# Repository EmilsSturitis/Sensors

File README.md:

# Sensors
Single repo for all of the sensor and interface breakout pcb's

Altimeter
HW:
Based on the TE MS581 sensor.
FW:
Based on the STM32F411

OPA548_dev  
Programmable CC/CV PSU

CAN Breakout

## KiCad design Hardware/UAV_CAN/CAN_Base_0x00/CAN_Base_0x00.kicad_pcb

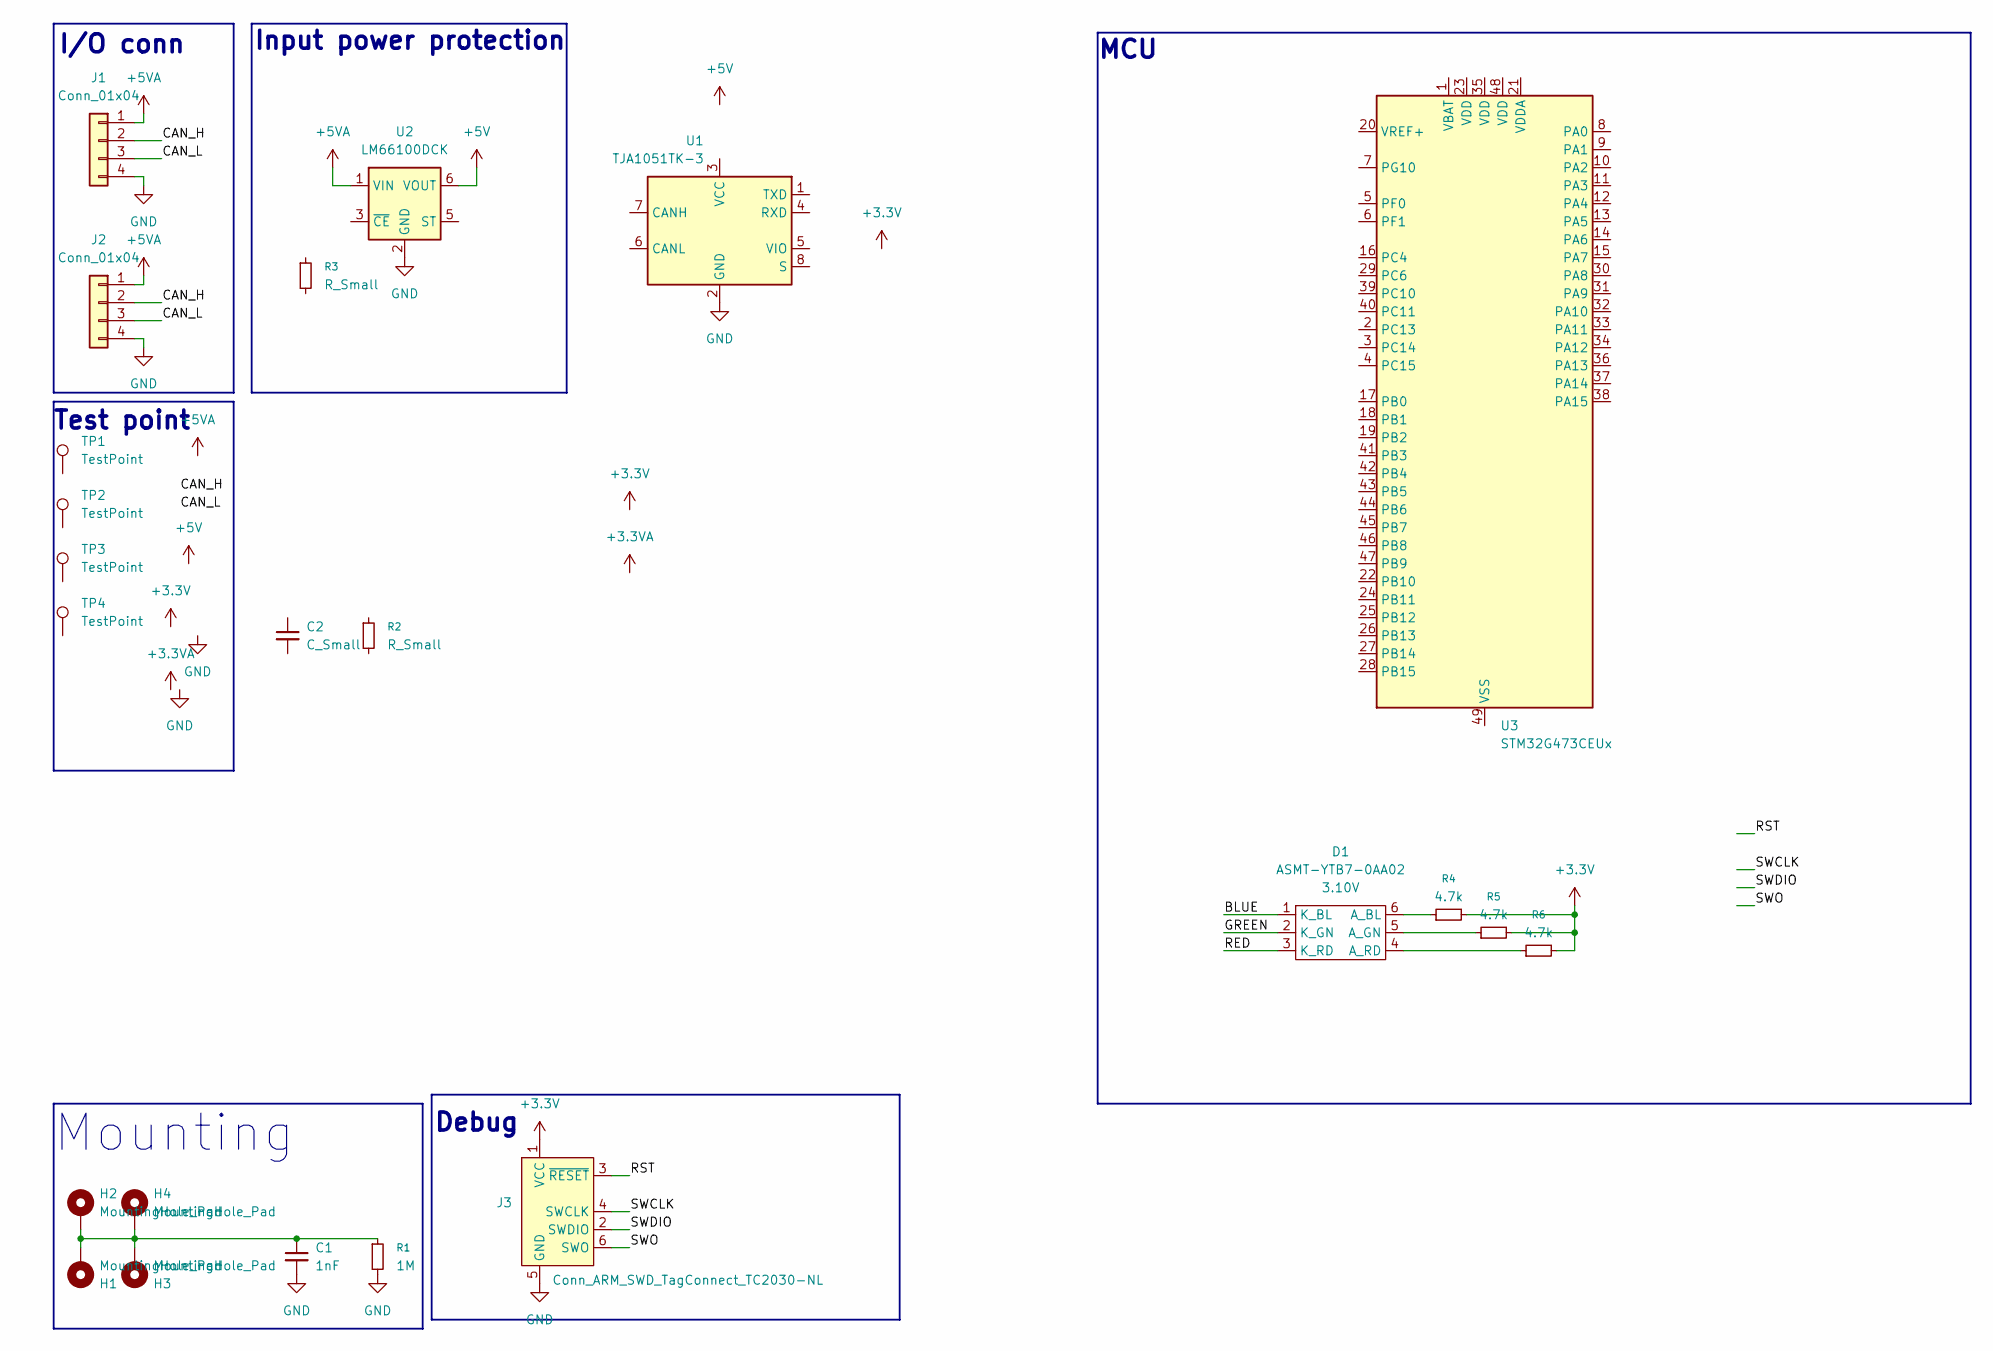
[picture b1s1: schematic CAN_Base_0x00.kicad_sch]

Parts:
C1: 1nF; C_0603_1608Metric
C2: C_Small; C_0603_1608Metric
D1: ASMT-YTB7-0AA02; ASMT-YTD7-0AA02
H1, H2, H3, H4: MountingHole_Pad; MountingHole_2.7mm_M2.5_Pad_Via
J1, J2: Conn_01x04; JST_GH_SM04B-GHS-TB_1x04-1MP_P1.25mm_Horizontal
J3: Conn_ARM_SWD_TagConnect_TC2030-NL; Tag-Connect_TC2030-IDC-NL_2x03_P1.27mm_Vertical
R1: 1M; R_0603_1608Metric
R2, R3: R_Small; R_0603_1608Metric
R4, R5, R6: 4.7k; R_0603_1608Metric
TP1, TP2, TP3, TP4: TestPoint; TestPoint_Pad_D1.0mm
U1: TJA1051TK-3; HVSON-8-1EP_3x3mm_P0.65mm_EP1.6x2.4mm
U2: LM66100DCK; SOT-363_SC-70-6
U3: STM32G473CEUx; QFN-48-1EP_7x7mm_P0.5mm_EP5.6x5.6mm

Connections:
+3.3V: J3.1 (VCC), R4.2, R5.2, R6.2
+5V: U2.6 (VOUT)
+5VA: J1.1, J2.1, U2.1 (VIN)
/BLUE: D1.1 (K_BL)
/CAN_H: J1.2, J2.2
/CAN_L: J1.3, J2.3
/GREEN: D1.2 (K_GN)
/RED: D1.3 (K_RD)
/RST: J3.3 (~RESET)
/SWCLK: J3.4 (SWCLK)
/SWDIO: J3.2 (SWDIO)
/SWO: J3.6 (SWO)
GND: C1.2, J1.4, J2.4, J3.5 (GND), R1.2, U1.2 (GND), U1.9 (GND), U2.2 (GND)
unnamed: C1.1, H1.1, H2.1, H3.1, H4.1, R1.1
unnamed: D1.6 (A_BL), R4.1
unnamed: D1.5 (A_GN), R5.1
unnamed: D1.4 (A_RD), R6.1

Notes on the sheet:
MCU
I/O conn
Test point
Input power protection
Debug
Mounting

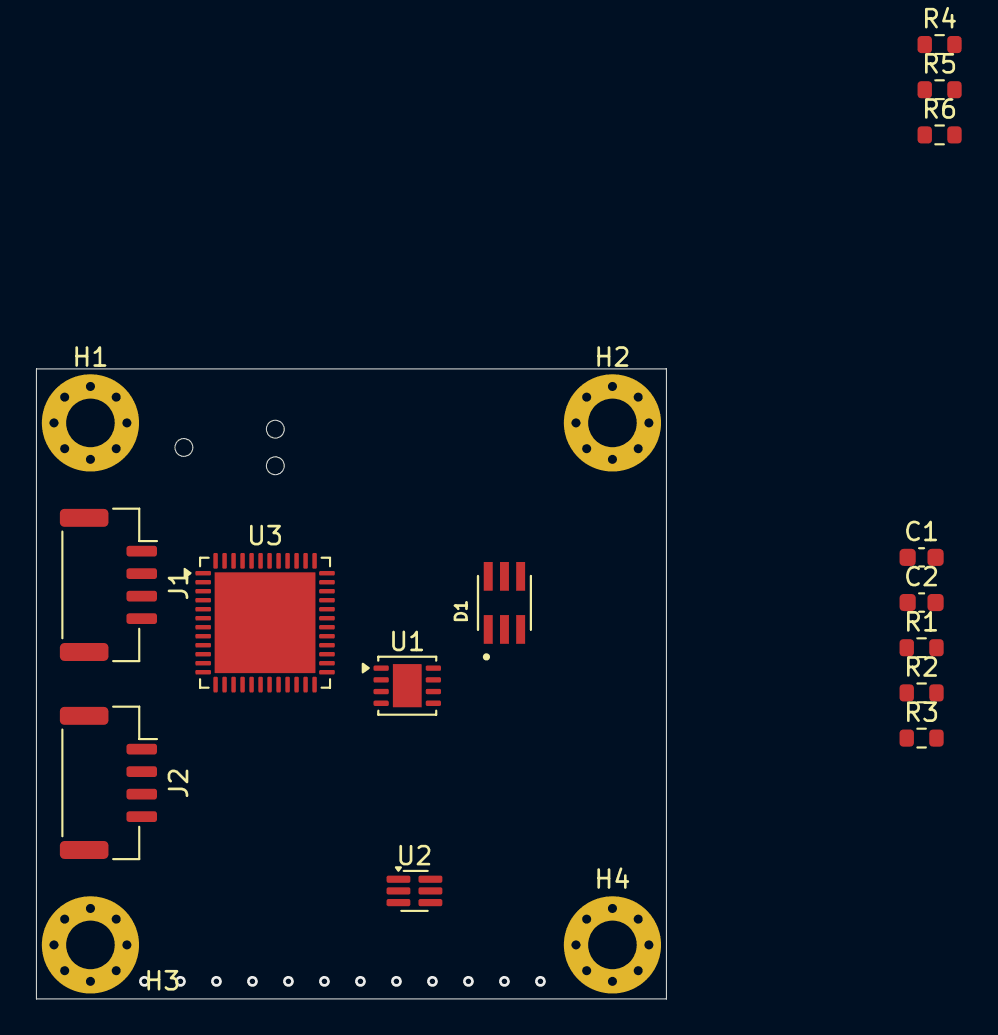
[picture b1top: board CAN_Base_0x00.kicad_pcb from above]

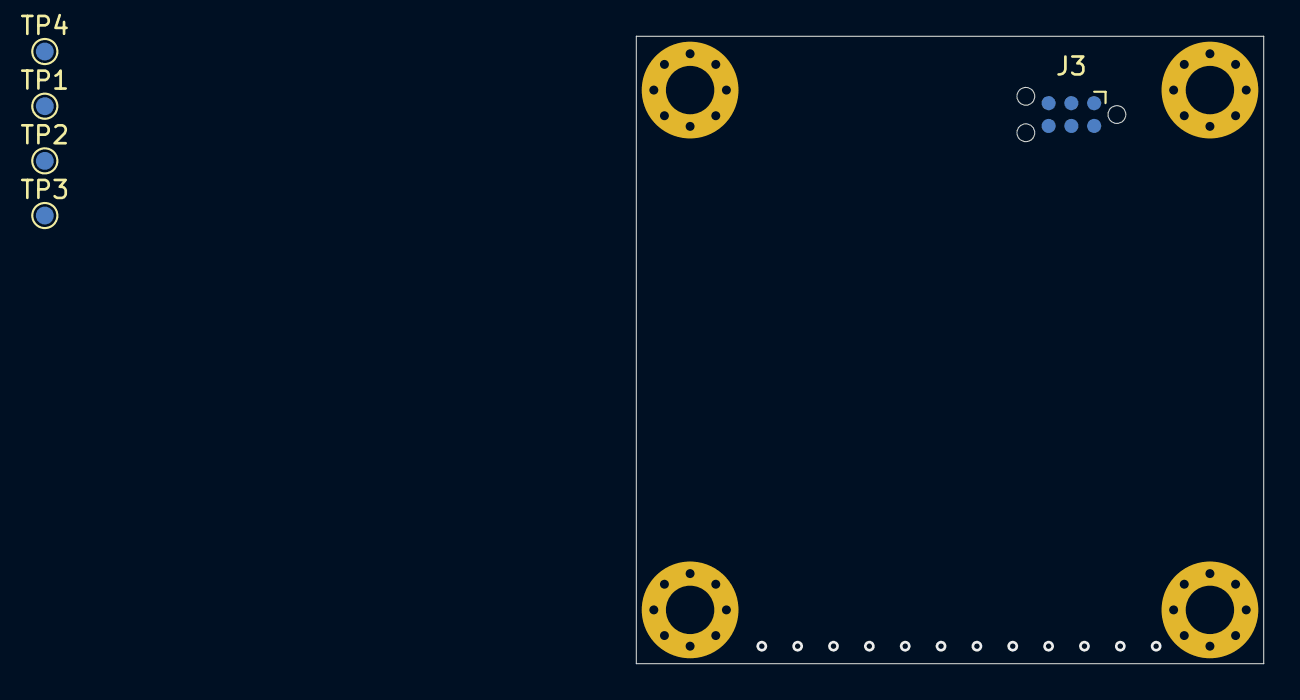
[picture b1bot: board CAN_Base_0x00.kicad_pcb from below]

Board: 2 copper layers, 35.0 x 35.0 mm, 23 parts (5 on the bottom side), 9 nets.

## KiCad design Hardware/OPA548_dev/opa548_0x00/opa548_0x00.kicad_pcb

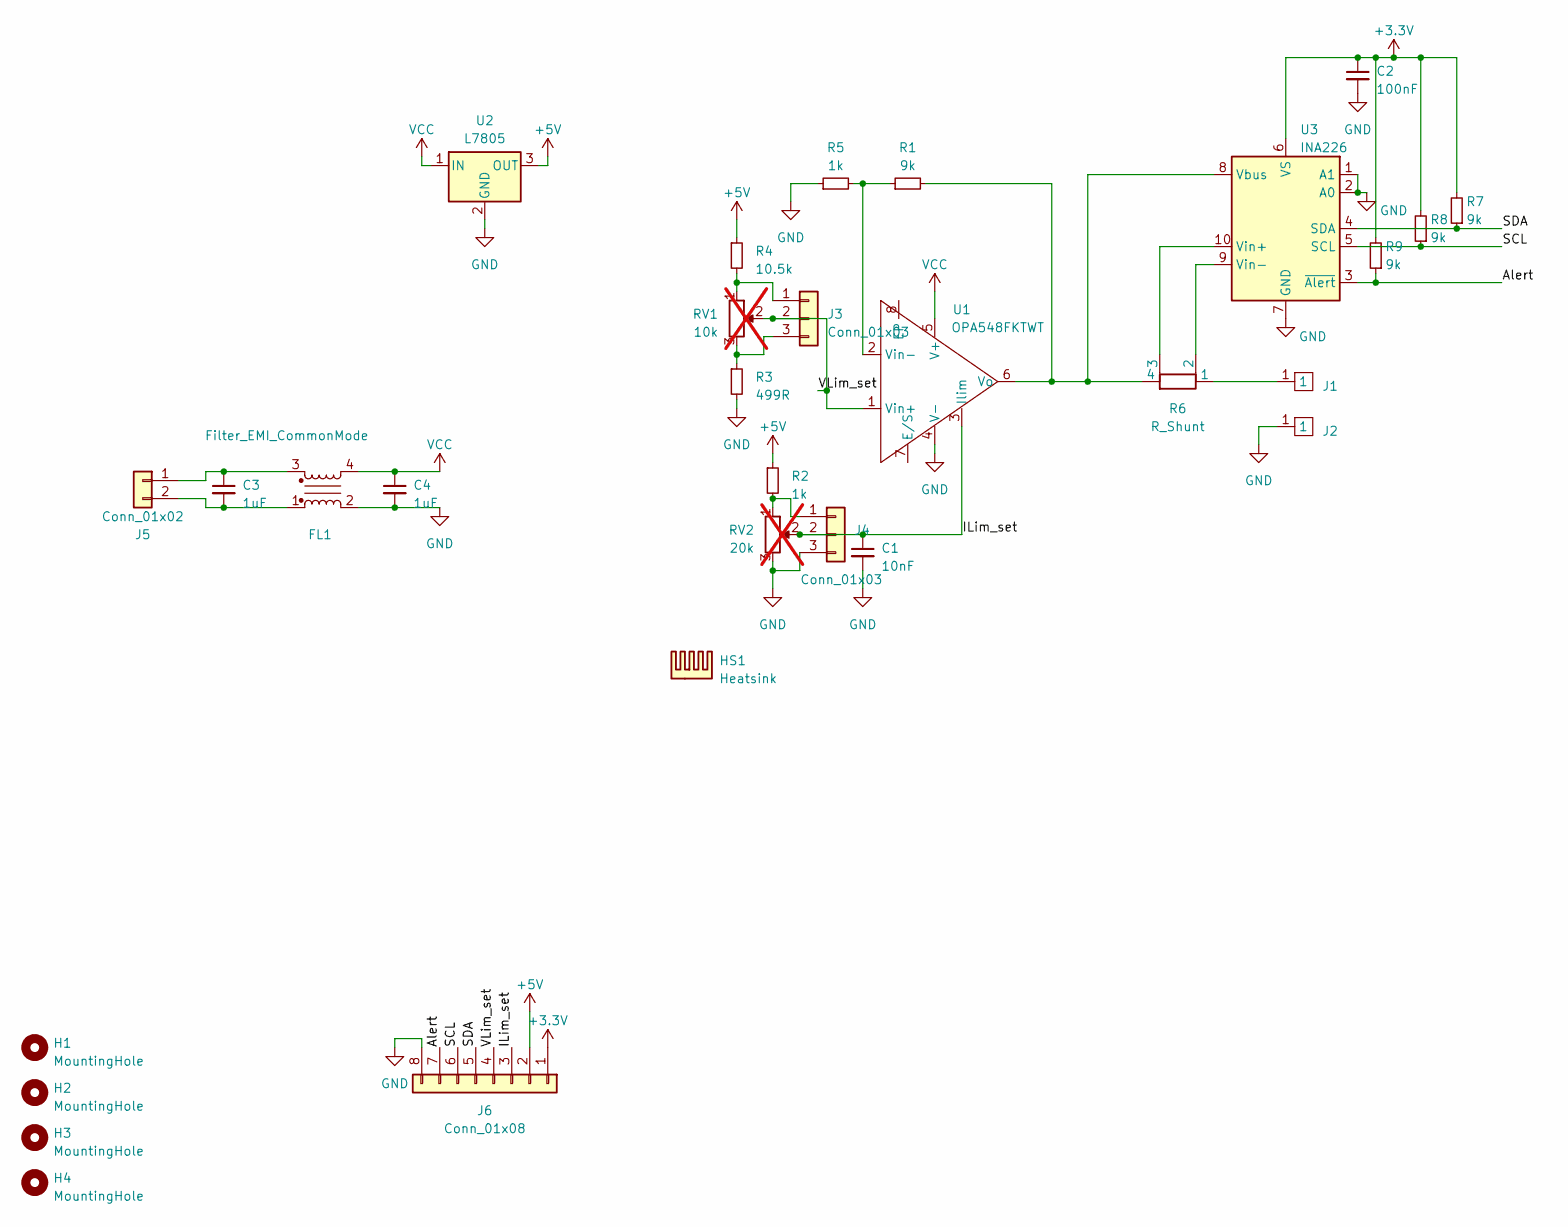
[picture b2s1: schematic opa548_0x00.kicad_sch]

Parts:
C1: 10nF; C_0805_2012Metric
C2: 100nF; C_0805_2012Metric
C3, C4: 1uF; C_1210_3225Metric
FL1: Filter_EMI_CommonMode; P0420NL
H1, H2, H3, H4: MountingHole; MountingHole_3.7mm
HS1: Heatsink; Heatsink_38x38mm_SpringFixation
J1, J2: CalTest_CT3151
J3, J4: Conn_01x03; JST_XH_B3B-XH-A_1x03_P2.50mm_Vertical
J5: Conn_01x02; TerminalBlock_bornier-2_P5.08mm
J6: Conn_01x08; PinHeader_1x08_P2.00mm_Vertical
R1, R7, R8, R9: 9k; R_0805_2012Metric
R2, R5: 1k; R_0805_2012Metric
R3: 499R; R_0805_2012Metric
R4: 10.5k; R_0805_2012Metric
R6: R_Shunt; R_Shunt_Vishay_WSKW0612
RV1: 10k; Potentiometer_Alpha_RD901F-40-00D_Single_Vertical_CircularH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; not fitted
RV2: 20k; Potentiometer_Alpha_RD901F-40-00D_Single_Vertical_CircularH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; not fitted
U1: OPA548FKTWT; TO-263-7_TabPin8
U2: L7805; TO-220F-3_Vertical
U3: INA226; VSSOP-10_3x3mm_P0.5mm

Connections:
+3.3V: C2.1, J6.1, R7.2, R8.2, R9.2, U3.6 (VS)
+5V: J6.2, R2.1, R4.1, U2.3 (OUT)
/Alert: J6.7, R9.1, U3.3 (~Alert)
/ILim_set: C1.1, J4.2, J6.3, RV2.2, U1.3 (Ilim)
/SCL: J6.6, R8.1, U3.5 (SCL)
/SDA: J6.5, R7.1, U3.4 (SDA)
/VLim_set: J3.2, J6.4, RV1.2, U1.1 (Vin+)
GND: C1.2, C2.2, C4.2, FL1.2, J2.1, J4.3, J6.8, R3.2, R5.1, RV2.3, U1.4 (V-), U2.2 (GND), U3.1 (A1), U3.2 (A0), U3.7 (GND)
unnamed: J1.1, R6.1
unnamed: J3.1, R4.2, RV1.1
unnamed: J3.3, R3.1, RV1.3
unnamed: J4.1, R2.2, RV2.1
unnamed: C3.1, FL1.3, J5.1
unnamed: C3.2, FL1.1, J5.2
unnamed: R1.1, R5.2, U1.2 (Vin-)
unnamed: R1.2, R6.4, U1.6 (Vo), U3.8 (Vbus)
unnamed: R6.3, U3.10 (Vin+)
unnamed: R6.2, U3.9 (Vin-)
VCC: C4.1, FL1.4, U1.5 (V+), U2.1 (IN)

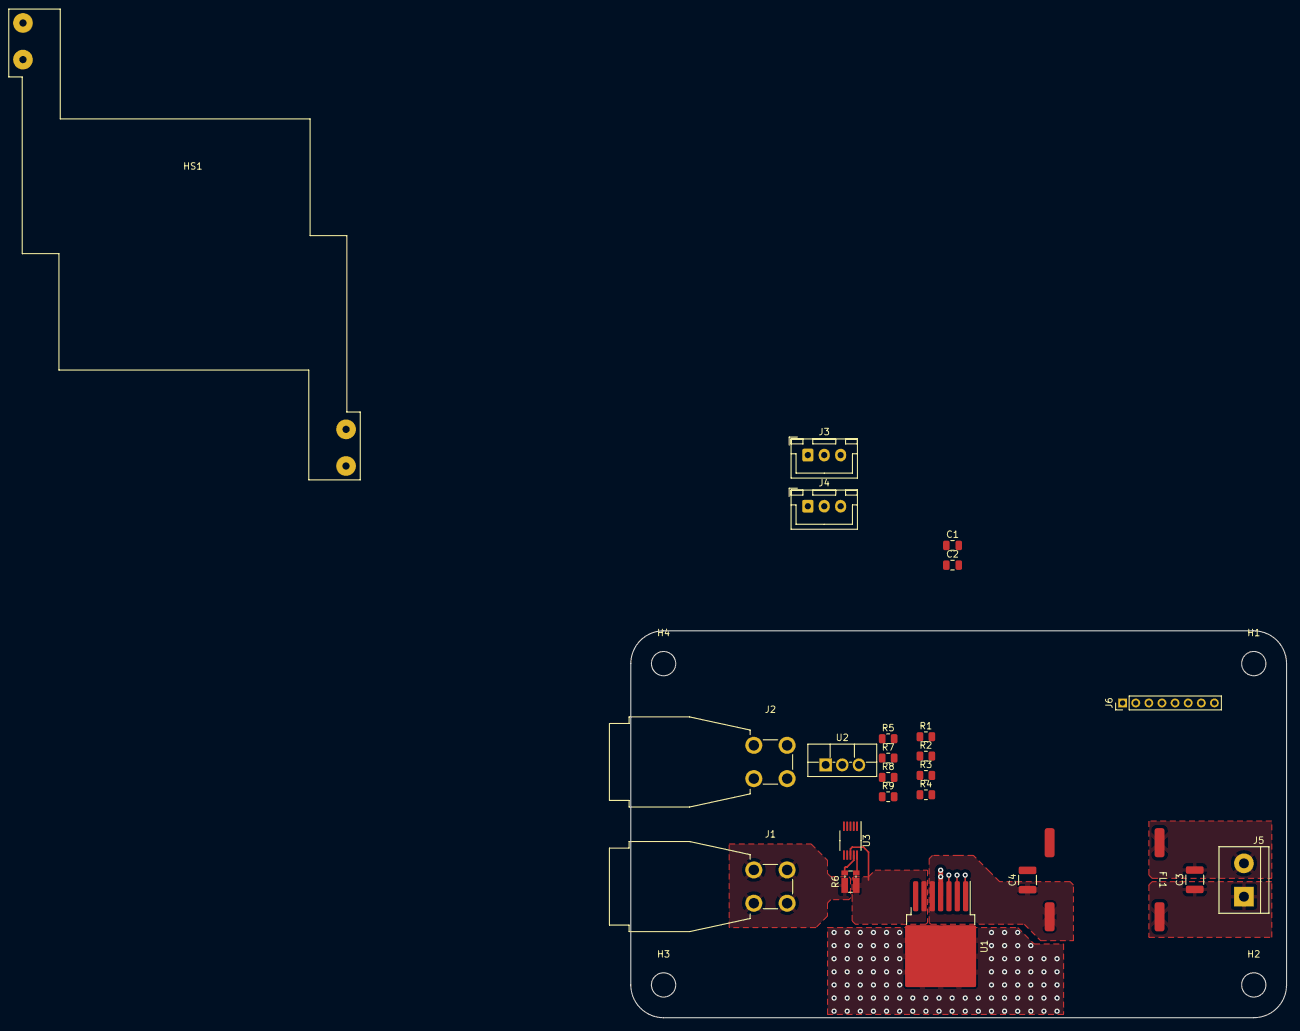
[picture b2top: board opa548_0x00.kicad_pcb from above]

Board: 2 copper layers, 100.0 x 59.0 mm, 28 parts (0 on the bottom side), 19 nets.

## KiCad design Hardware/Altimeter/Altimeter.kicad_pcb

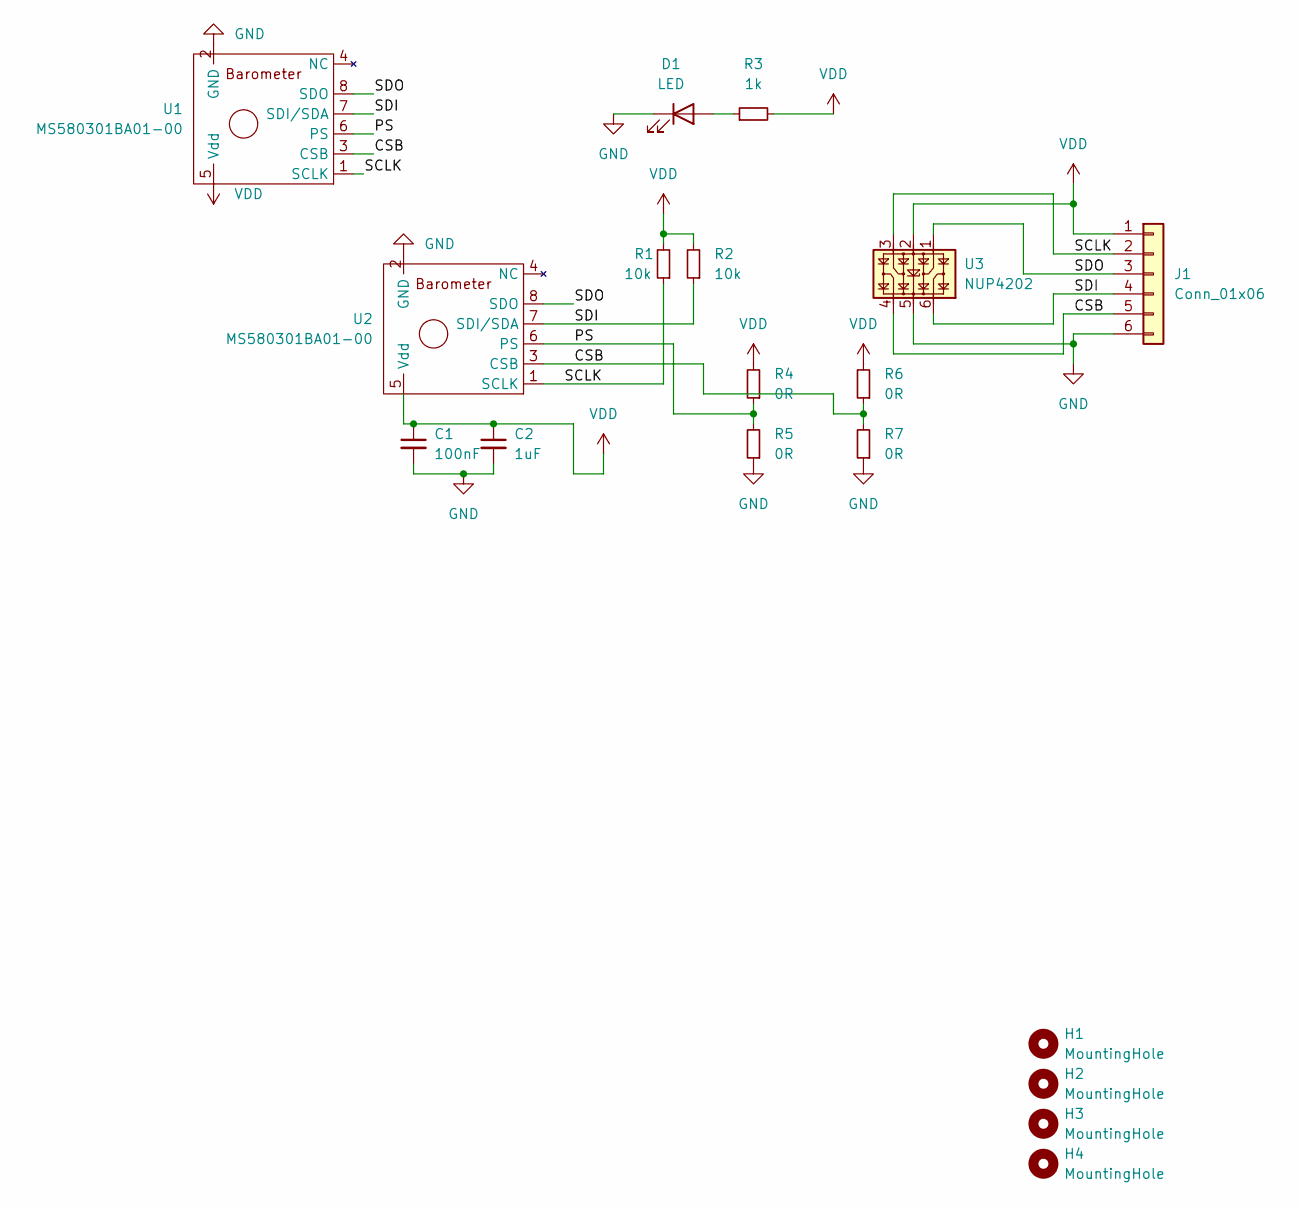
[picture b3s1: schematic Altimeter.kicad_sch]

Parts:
C1: 100nF; C_0805_2012Metric
C2: 1uF; C_0805_2012Metric
D1: LED; LED_PLCC-2
H1, H2, H3, H4: MountingHole; MountingHole_3.2mm_M3
J1: Conn_01x06; PinHeader_1x06_P2.54mm_Horizontal
R1, R2: 10k; R_0805_2012Metric
R3: 1k; R_0805_2012Metric
R4, R5, R6, R7: 0R; R_0805_2012Metric
U1, U2: MS580301BA01-00
U3: NUP4202; SOT-363_SC-70-6

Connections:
/CSB: J1.5, R6.1, R7.2, U1.3 (CSB), U2.3 (CSB), U3.4
/PS: R4.1, R5.2, U1.6 (PS), U2.6 (PS)
/SCLK: J1.2, R1.1, U1.1 (SCLK), U2.1 (SCLK), U3.3
/SDI: J1.4, R2.1, U1.7 (SDI/SDA), U2.7 (SDI/SDA), U3.6
/SDO: J1.3, U1.8 (SDO), U2.8 (SDO), U3.1
GND: C1.2, C2.2, D1.1 (K), J1.6, R5.1, R7.1, U1.2 (GND), U2.2 (GND), U3.5
unnamed: D1.2 (A), R3.1
VDD: C1.1, C2.1, J1.1, R1.2, R2.2, R3.2, R4.2, R6.2, U1.5 (Vdd), U2.5 (Vdd), U3.2

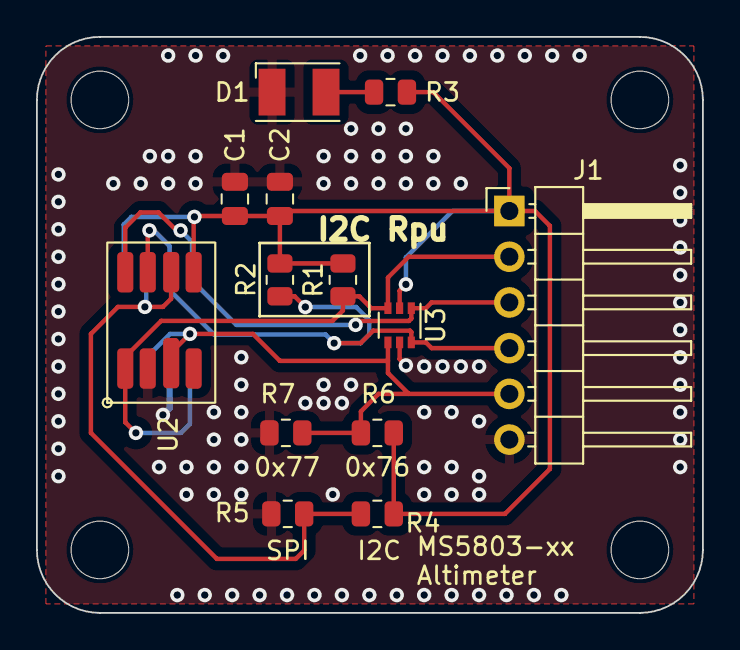
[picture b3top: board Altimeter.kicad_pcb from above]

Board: 2 copper layers, 37.0 x 32.0 mm, 18 parts (1 on the bottom side), 8 nets.

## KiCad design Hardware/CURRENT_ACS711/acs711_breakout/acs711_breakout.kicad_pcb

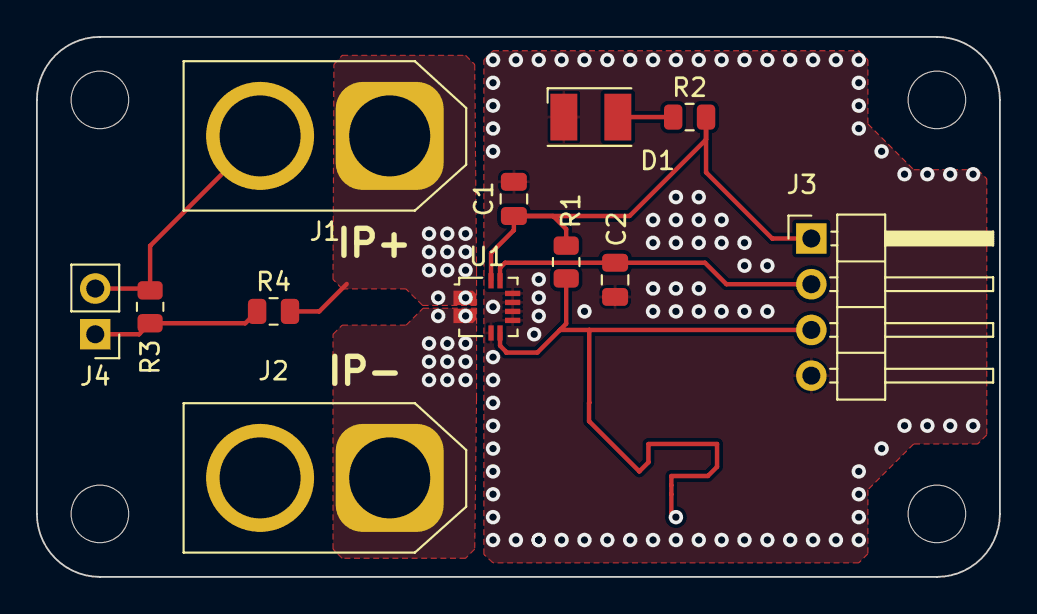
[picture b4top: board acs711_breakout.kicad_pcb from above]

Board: 2 copper layers, 53.5 x 30.0 mm, 16 parts (0 on the bottom side), 9 nets.

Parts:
C1: 100nF; C_0805_2012Metric
C2: DNP; C_0805_2012Metric
D1: LED; LED_PLCC-2
H1, H2, H3, H4: MountingHole; MountingHole_3.2mm_M3
J1: Conn_01x02; AMASS_XT60-M_1x02_P7.20mm_Vertical
J2: Conn_01x02; AMASS_XT60-F_1x02_P7.20mm_Vertical
J3: Conn_01x04; PinHeader_1x04_P2.54mm_Horizontal
J4: Conn_01x02; PinHeader_1x02_P2.54mm_Vertical
R1, R2: 1k; R_0805_2012Metric
R3, R4: R_Small; R_0805_2012Metric
U1: ACS711xEXLT-15AB; Allegro_QFN-12-10-1EP_3x3mm_P0.5mm

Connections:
GND: C1.2, C2.2, D1.1 (K), J3.4, U1.3 (GND), U1.5 (NC), U1.6 (NC), U1.7 (NC), U1.8 (NC)
unnamed: C2.1, J3.2, U1.9 (VIOUT)
unnamed: D1.2 (A), R2.1
unnamed: J1.2, J2.2, J4.2, R3.1
unnamed: J3.3, R1.2, U1.4 (~FAULT)
unnamed: J4.1, R3.2, R4.1
unnamed: J1.1, R4.2, U1.1 (IP+)
unnamed: J2.1, U1.2 (IP-)
VCC: C1.1, J3.1, R1.1, R2.2, U1.10 (VCC)

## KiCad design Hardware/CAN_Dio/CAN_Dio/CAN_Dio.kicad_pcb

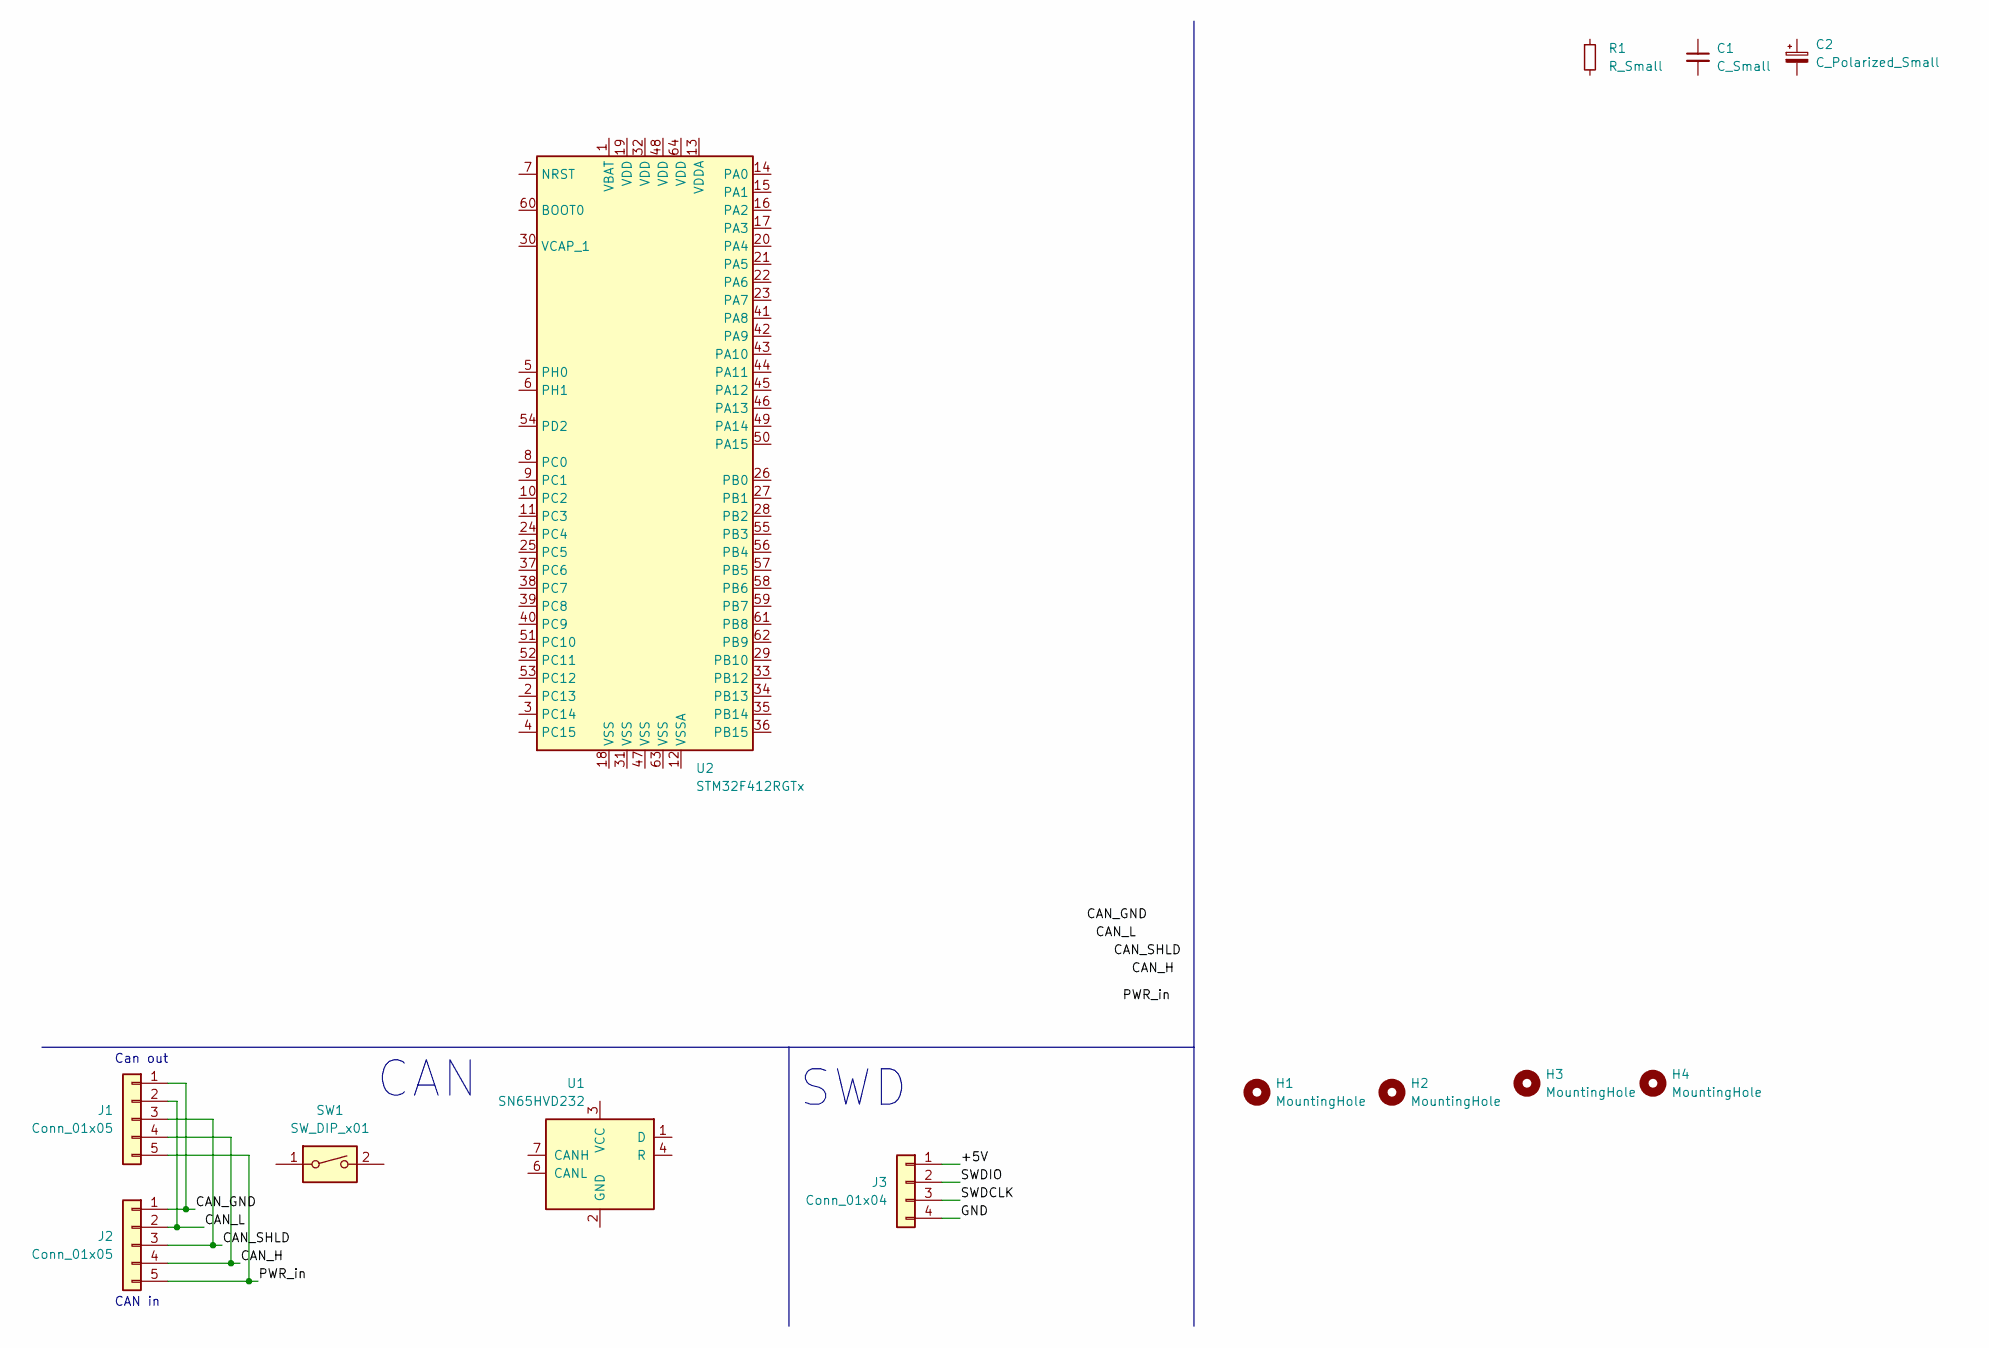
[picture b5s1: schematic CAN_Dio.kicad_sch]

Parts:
C1: C_Small; C_0805_2012Metric
C2: C_Polarized_Small
H1, H2, H3, H4: MountingHole; MountingHole_3.5mm
J1, J2: Conn_01x05; JST_XH_B5B-XH-A_1x05_P2.50mm_Vertical
J3: Conn_01x04; PinSocket_1x04_P2.54mm_Vertical
R1: R_Small; R_0805_2012Metric
SW1: SW_DIP_x01; SW_DIP_SPSTx01_Piano_10.8x4.1mm_W7.62mm_P2.54mm
U1: SN65HVD232; SOIC-8_3.9x4.9mm_P1.27mm
U2: STM32F412RGTx; LQFP-64_10x10mm_P0.5mm

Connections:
/+5V: J3.1
/CAN_GND: J1.1, J2.1
/CAN_H: J1.4, J2.4
/CAN_L: J1.2, J2.2
/CAN_SHLD: J1.3, J2.3
/GND: J3.4
/PWR_in: J1.5, J2.5
/SWDCLK: J3.3
/SWDIO: J3.2

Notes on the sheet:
CAN in
CAN
SWD
Can out

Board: 2 copper layers, 12 parts (0 on the bottom side), 5 nets, no tracks yet.

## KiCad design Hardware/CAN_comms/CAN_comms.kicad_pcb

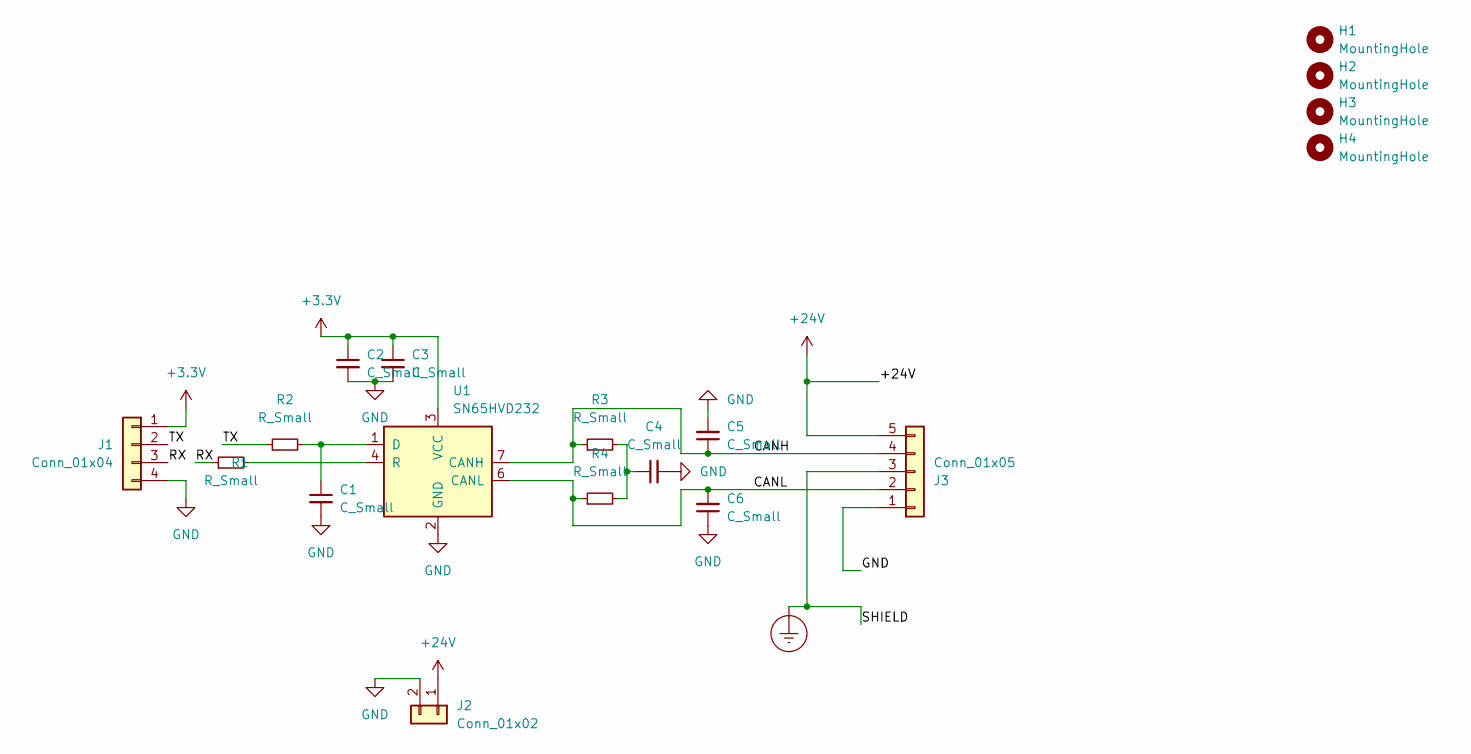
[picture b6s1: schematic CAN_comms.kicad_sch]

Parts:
C1, C2, C3, C4, C5, C6: C_Small; C_0805_2012Metric
H1, H2, H3, H4: MountingHole; MountingHole_3.2mm_M3_Pad_Via
J1: Conn_01x04; JST_XH_S4B-XH-A_1x04_P2.50mm_Horizontal
J2: Conn_01x02; JST_XH_S2B-XH-A_1x02_P2.50mm_Horizontal
J3: Conn_01x05; JST_XH_S5B-XH-A_1x05_P2.50mm_Horizontal
R1, R2: R_Small; R_0805_2012Metric
R3, R4: R_Small; R_1210_3225Metric
U1: SN65HVD232; SOIC-8_3.9x4.9mm_P1.27mm

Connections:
+3.3V: C2.1, C3.1, J1.1, U1.3 (VCC)
+24V: J2.1, J3.5
/CANH: C5.1, J3.4, R3.1, U1.7 (CANH)
/CANL: C6.2, J3.2, R4.1, U1.6 (CANL)
/RX: J1.3, R1.1
/TX: J1.2, R2.1
Earth_Protective: J3.3
GND: C1.2, C2.2, C3.2, C4.2, C5.2, C6.1, J1.4, J2.2, J3.1, U1.2 (GND)
unnamed: C1.1, R2.2, U1.1 (D)
unnamed: C4.1, R3.2, R4.2
unnamed: R1.2, U1.4 (R)

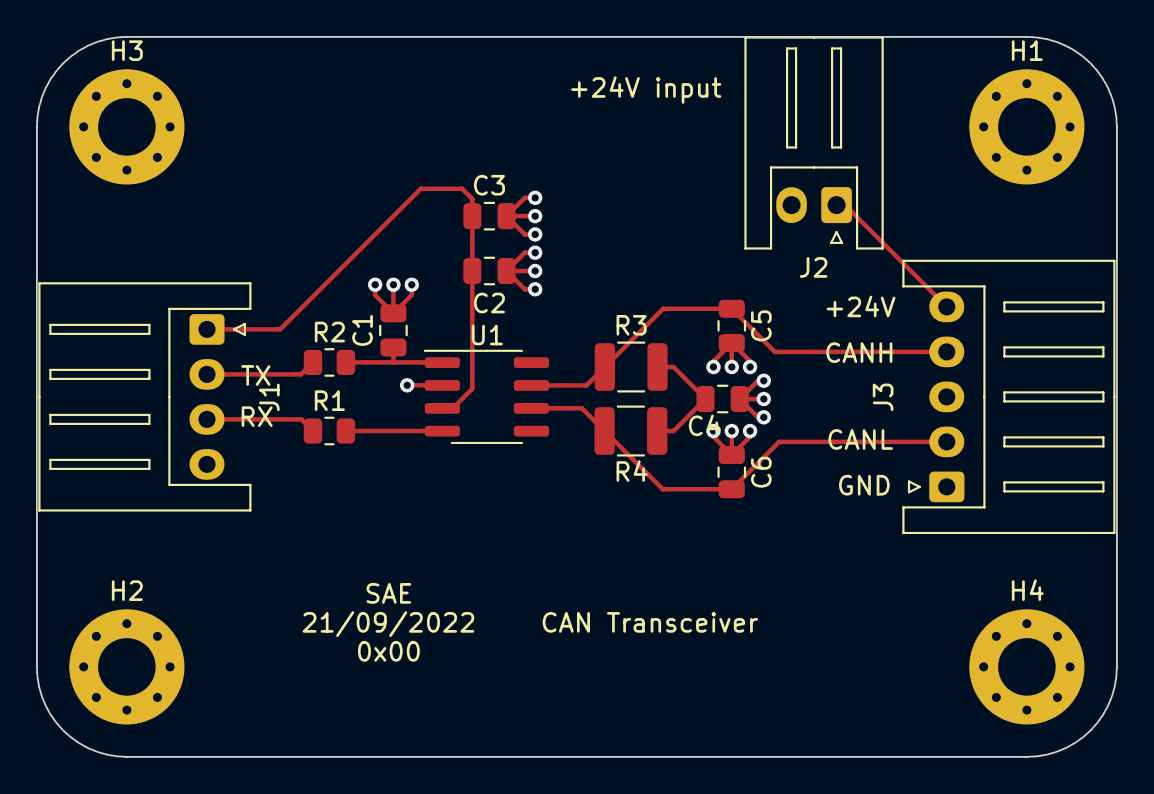
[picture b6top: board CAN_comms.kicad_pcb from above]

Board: 2 copper layers, 60.0 x 40.0 mm, 18 parts (0 on the bottom side), 10 nets.

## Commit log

2022-09-21 innital commit of can RX/TX chip
2022-10-06 Dio board
    Beginning of Dio board design and the definition of CanOpen node pcb size(60x90mm), input, output, SWD and uart connector placement
2022-10-18 add random pcs for Dio and initial commit fo acs711 breakout
2023-01-22 layout and some stitching vias
2023-01-22 added the altimeter project
2023-01-22 Finished the layout for altimeter
2023-01-23 Last version of altimeter and ACS7111 pcbs
2023-02-10 component update
2023-02-17 start of altimeter FW
2023-02-21 updates to I2C driver
2023-03-06 some small updates
2023-03-18 more work with drivers, with help og ChatGPT
2023-04-06 update to altimeter pcb
2023-11-02 added opa548
2023-12-03 added ads
2024-11-18 soft update
2025-07-17 update to Readme
2026-05-12 New project base
